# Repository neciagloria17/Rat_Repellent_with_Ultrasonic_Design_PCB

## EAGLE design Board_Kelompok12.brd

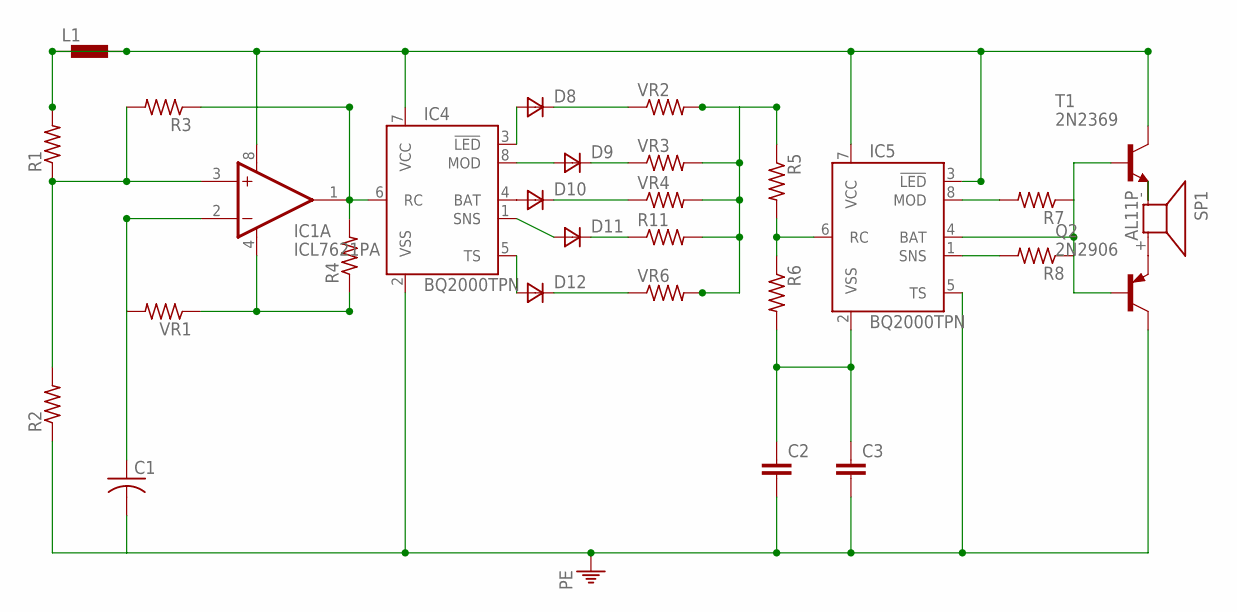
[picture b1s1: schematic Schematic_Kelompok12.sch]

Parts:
C1: C-US025-030X050; C025-030X050
C2, C3: C-EU025-030X050; C025-030X050
D8, D9, D10, D11, D12: D_E2L; E2LINE
IC1: ICL7621PA; DIL08
IC4, IC5: BQ2000TPN; DIL08
L1: DR1030
Q2: 2N2906; TO18
R1, R11: R-US_0204/7; 0204/7
R2, R3, R4, R5, R6, R7, R8: R-US_0309/12; 0309/12
SP1: AL11P
T1: 2N2369; TO18
VR1: R-US_0309/12; 0309/12
VR2, VR3, VR4, VR6: R-US_0204/7; 0204/7

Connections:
unnamed: IC1.8 (V+), IC4.7 (VCC), IC5.3 (!LED), IC5.7 (VCC), L1.1, L1.2, R1.2, T1.3 (C)
unnamed: IC1.3 (+IN), R1.1, R2.2, R3.2
unnamed: IC1.1 (OUT), IC4.6 (RC), R3.1, R4.2
unnamed: D9.1 (C), VR3.1
unnamed: C1.1, IC1.2 (-IN), VR1.2
unnamed: IC1.4 (V-), R4.1, VR1.1
unnamed: IC5.8 (MOD), R7.2
unnamed: D8.2 (A), IC4.3 (!LED)
unnamed: D9.2 (A), IC4.8 (MOD)
unnamed: D10.2 (A), IC4.4 (BAT)
unnamed: D11.2 (A), IC4.1 (SNS)
unnamed: D12.2 (A), IC4.5 (TS)
unnamed: D11.1 (C), R11.1
unnamed: Q2.1 (E), SP1.+ (2)
unnamed: D12.1 (C), VR6.1
unnamed: D10.1 (C), VR4.1
unnamed: R5.1, R11.2, VR2.2, VR3.2, VR4.2, VR6.2
unnamed: IC5.6 (RC), R5.2, R6.1
unnamed: C2.1, C3.1, IC5.2 (VSS), R6.2
unnamed: IC5.1 (SNS), R8.2
unnamed: SP1.- (1), T1.1 (E)
unnamed: IC5.4 (BAT), Q2.2 (B), R7.1, R8.1, T1.2 (B)
PE: C1.2, C2.2, C3.2, IC4.2 (VSS), IC5.5 (TS), Q2.3 (C), R2.1
VR2: D8.1 (C), VR2.1

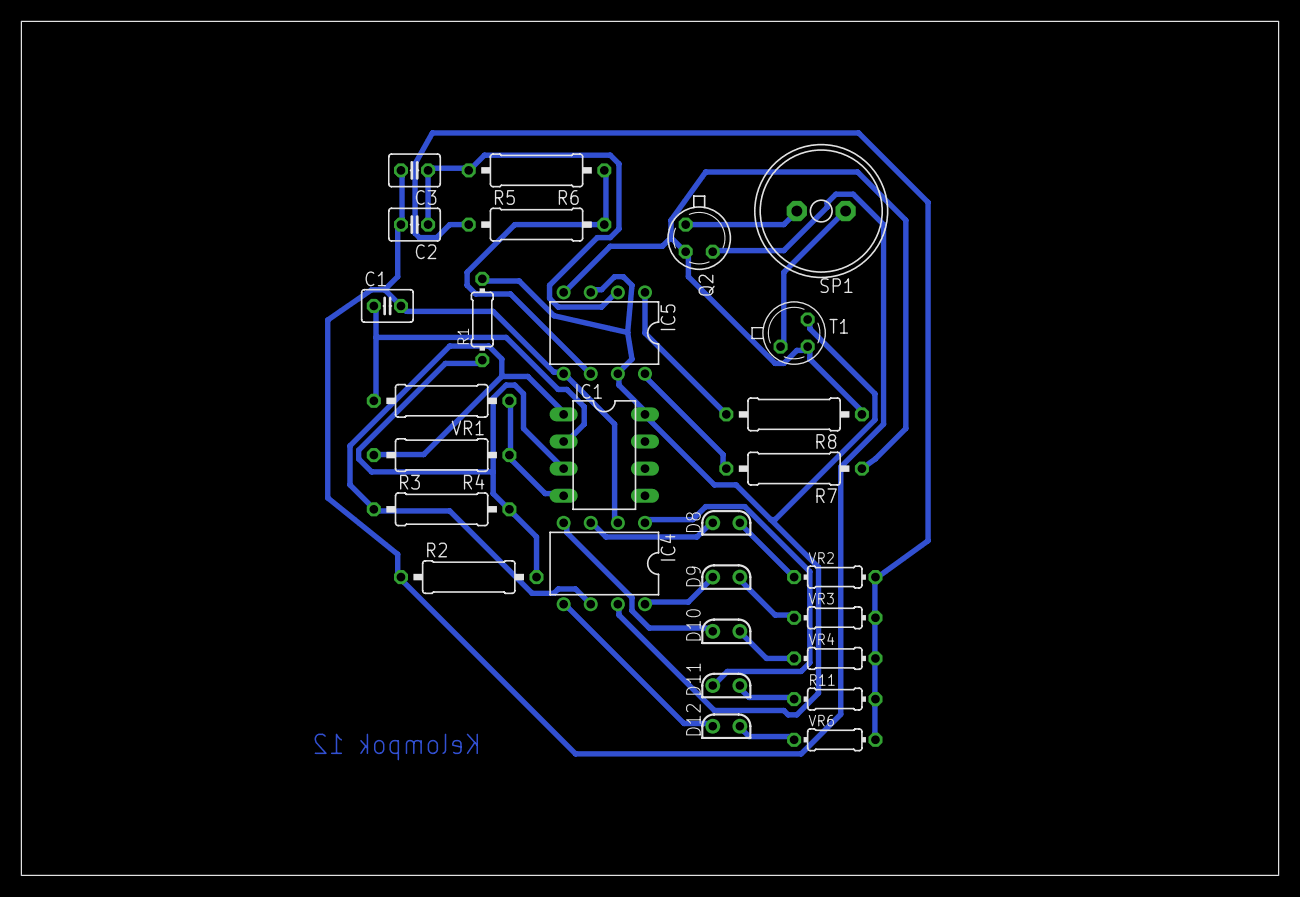
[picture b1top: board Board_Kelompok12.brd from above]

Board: 2 copper layers, 117.8 x 80.0 mm, 28 parts (0 on the bottom side), 24 nets.
